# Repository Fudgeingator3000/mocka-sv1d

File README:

This is the MOCKA sv1d.
its a small esp32-c5 powerd device with an external antenna. it was inspired by the maurader mini by JustCallMeKoKo.
it has IR, dualband wifi and bluetooth.
it has an external SMA connector for an external antenna
it currently has no firmware for it

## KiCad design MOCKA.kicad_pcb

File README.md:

This is the MOCKA sv1d.
its a small esp32-c5 powerd device with an external antenna. it was inspired by the maurader mini by JustCallMeKoKo.
it has IR, dualband wifi and bluetooth.
it has an external SMA connector for an external antenna
it currently has no firmware for it.
SCHEMATIC:

PCB:

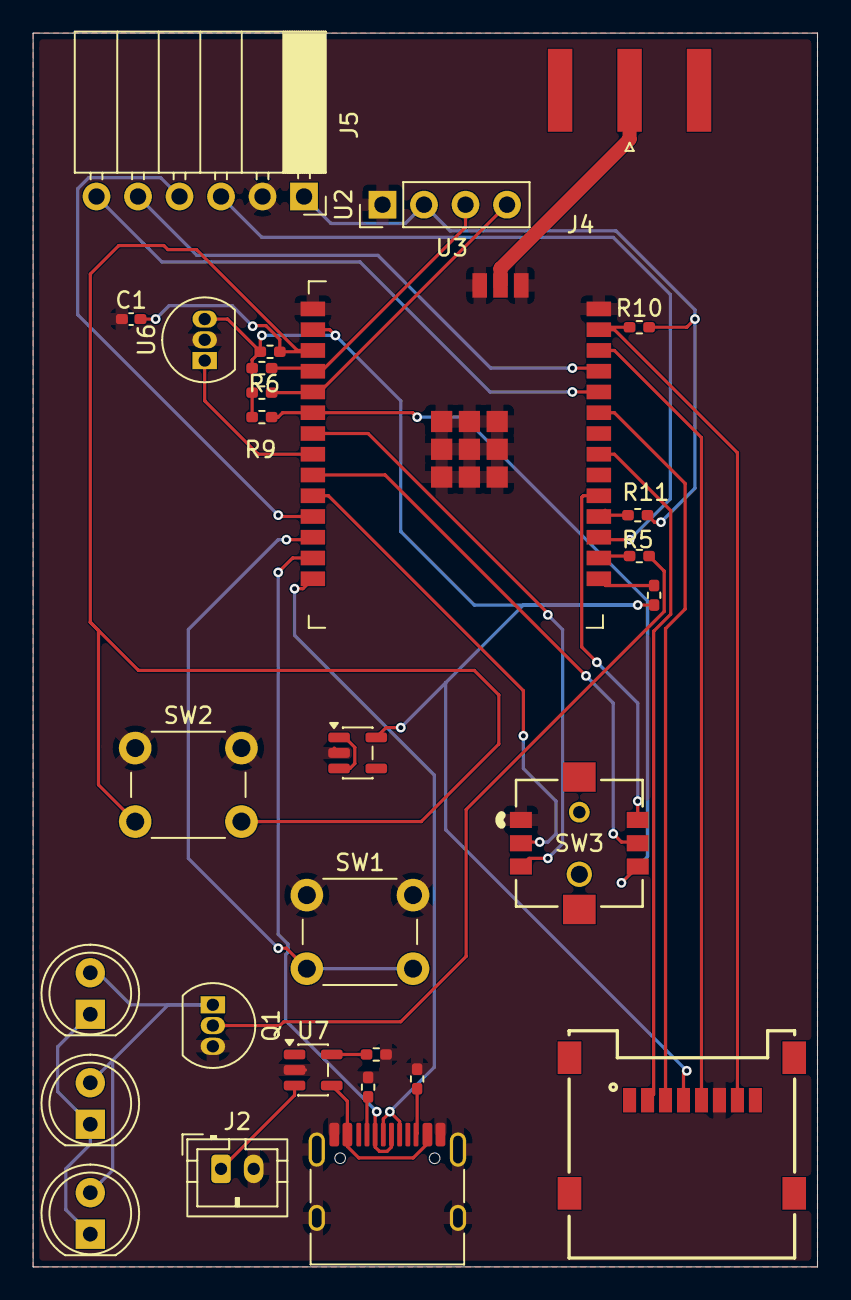
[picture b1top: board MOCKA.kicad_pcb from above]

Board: 2 copper layers, 48.0 x 75.5 mm, 29 parts (0 on the bottom side), 34 nets.

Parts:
C1: C_US; C_0402_1005Metric_Pad0.74x0.62mm_HandSolder
D1, D3, D4: SFH4546; LED_D5.0mm_IRGrey
J1: Micro_SD_Card_Det2; 693072010801
J2: Conn_01x02; JST_PH_B2B-PH-K_1x02_P2.00mm_Vertical
J3: USB_C_Receptacle; USB_C_Receptacle_HRO_TYPE-C-31-M-12
J4: Conn_01x01; SMA_Amphenol_132289_EdgeMount
J5: Conn_01x06; PinSocket_1x06_P2.54mm_Horizontal
Q1: BS170; TO-92_Inline
R1: 2k; R_0402_1005Metric_Pad0.72x0.64mm_HandSolder
R3, R4: 5.1k; R_0402_1005Metric_Pad0.72x0.64mm_HandSolder
R5: 100R; R_0402_1005Metric_Pad0.72x0.64mm_HandSolder
R6, R7: 4.7k; R_0402_1005Metric_Pad0.72x0.64mm_HandSolder
R8, R9, R10, R11, R12: 10k; R_0402_1005Metric_Pad0.72x0.64mm_HandSolder
SW1, SW2: SW_Push; SW_PUSH_6mm_H4.3mm
SW3: SKRHABE010; SKRHABE010_ALPS
U2: ER_OLEDM0.91_1x-I2C; PinHeader_1x04_P2.54mm_Vertical
U3: ESP32-C5-WROOM-1U
U5: AP2112K-3.3; SOT-23-5
U6: TSOP382xx; TO-92_Inline
U7: MCP73831-2-OT; SOT-23-5

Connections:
+3V3: J1.4 (VDD), J5.1, R6.2, R7.2, R8.2, R9.2, R10.2, R11.2, R12.2, U2.2 (VCC), U3.2 (3V3), U5.5 (VOUT), U6.3 (Vs)
/BAT: J2.1, U7.3 (V_{BAT})
/EN: C1.2, R8.1, SW2.2, U3.3 (EN/CHIP_PU)
/GPIO0: R9.1, SW3.6, U3.6 (GPIO0)
/GPIO1: SW3.3, U3.7 (GPIO1)
/GPIO2: R6.1, U2.3 (SCL), U3.4 (GPIO2)
/GPIO3: R7.1, U2.4 (SDA), U3.5 (GPIO3)
/GPIO4: J5.3, U3.17 (GPIO4)
/GPIO5: R5.1, U3.16 (GPIO5)
/GPIO6: U3.8 (GPIO6), U6.1 (OUT)
/GPIO7: SW3.5, U3.9 (GPIO7)
/GPIO8: SW3.2, U3.10 (GPIO8)
/GPIO9: J5.4, U3.11 (GPIO9)
/GPIO10: SW1.2, U3.12 (GPIO10)
/GPIO11: J5.5, U3.25 (U0TXD/GPIO11)
/GPIO12: J5.6, U3.24 (U0RXD/GPIO12)
/GPIO13_D-: J3.A7 (D-), J3.B7 (D-), U3.13 (GPIO13/USB_D-)
/GPIO14_D+: J3.A6 (D+), J3.B6 (D+), U3.14 (GPIO14/USB_D+)
/GPIO15: SW3.4, U3.19 (GPIO15)
/GPIO23: J1.2 (DAT3/CD), U3.21 (GPIO23)
/GPIO24: J1.3 (CMD), U3.23 (GPIO24)
/GPIO25: J1.5 (CLK), U3.26 (GPIO25)
/GPIO26: J1.7 (DAT0), R10.1, U3.27 (GPIO26)
/GPIO27: R11.1, U3.18 (GPIO27)
/GPIO28: R12.1, U3.15 (GPIO28)
/RF_ANT: J4.1 (Pin_1_1), U3.31 (ANT2)
GNDD: C1.1, J1.6 (VSS), J2.2, J3.A1 (GND), J3.A12 (GND), J3.B1 (GND), J3.B12 (GND), J3.SH (SHIELD), J5.2, Q1.3 (S), R1.1, R3.2, R4.2, SW1.1, SW2.1, SW3.1, U2.1 (GND), U3.1 (GND), U3.28 (GND), U3.29 (GND), U3.30 (GND), U3.32 (GND), U5.2 (GND), U6.2 (GND), U7.2 (V_{SS})
unnamed: D1.2 (A), D3.2 (A), D4.2 (A), Q1.1 (D)
unnamed: J3.A5 (CC1), R3.1
unnamed: J3.B5 (CC2), R4.1
unnamed: Q1.2 (G), R5.2
unnamed: R1.2, U7.5 (PROG)
unnamed: J3.A4 (VBUS), J3.A9 (VBUS), J3.B4 (VBUS), J3.B9 (VBUS), U7.4 (V_{DD})
VCC: D1.1 (K), D3.1 (K), D4.1 (K), U5.1 (VIN), U5.3 (EN)

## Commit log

2026-05-27 these are the pcb files
2026-06-01 Add Bill of Materials (BOM) for components
    its the materials needed
2026-06-02 Add initial README for MOCKA sv1d device
2026-06-02 Update README with schematic and PCB details
    Added schematic and PCB images to README.
